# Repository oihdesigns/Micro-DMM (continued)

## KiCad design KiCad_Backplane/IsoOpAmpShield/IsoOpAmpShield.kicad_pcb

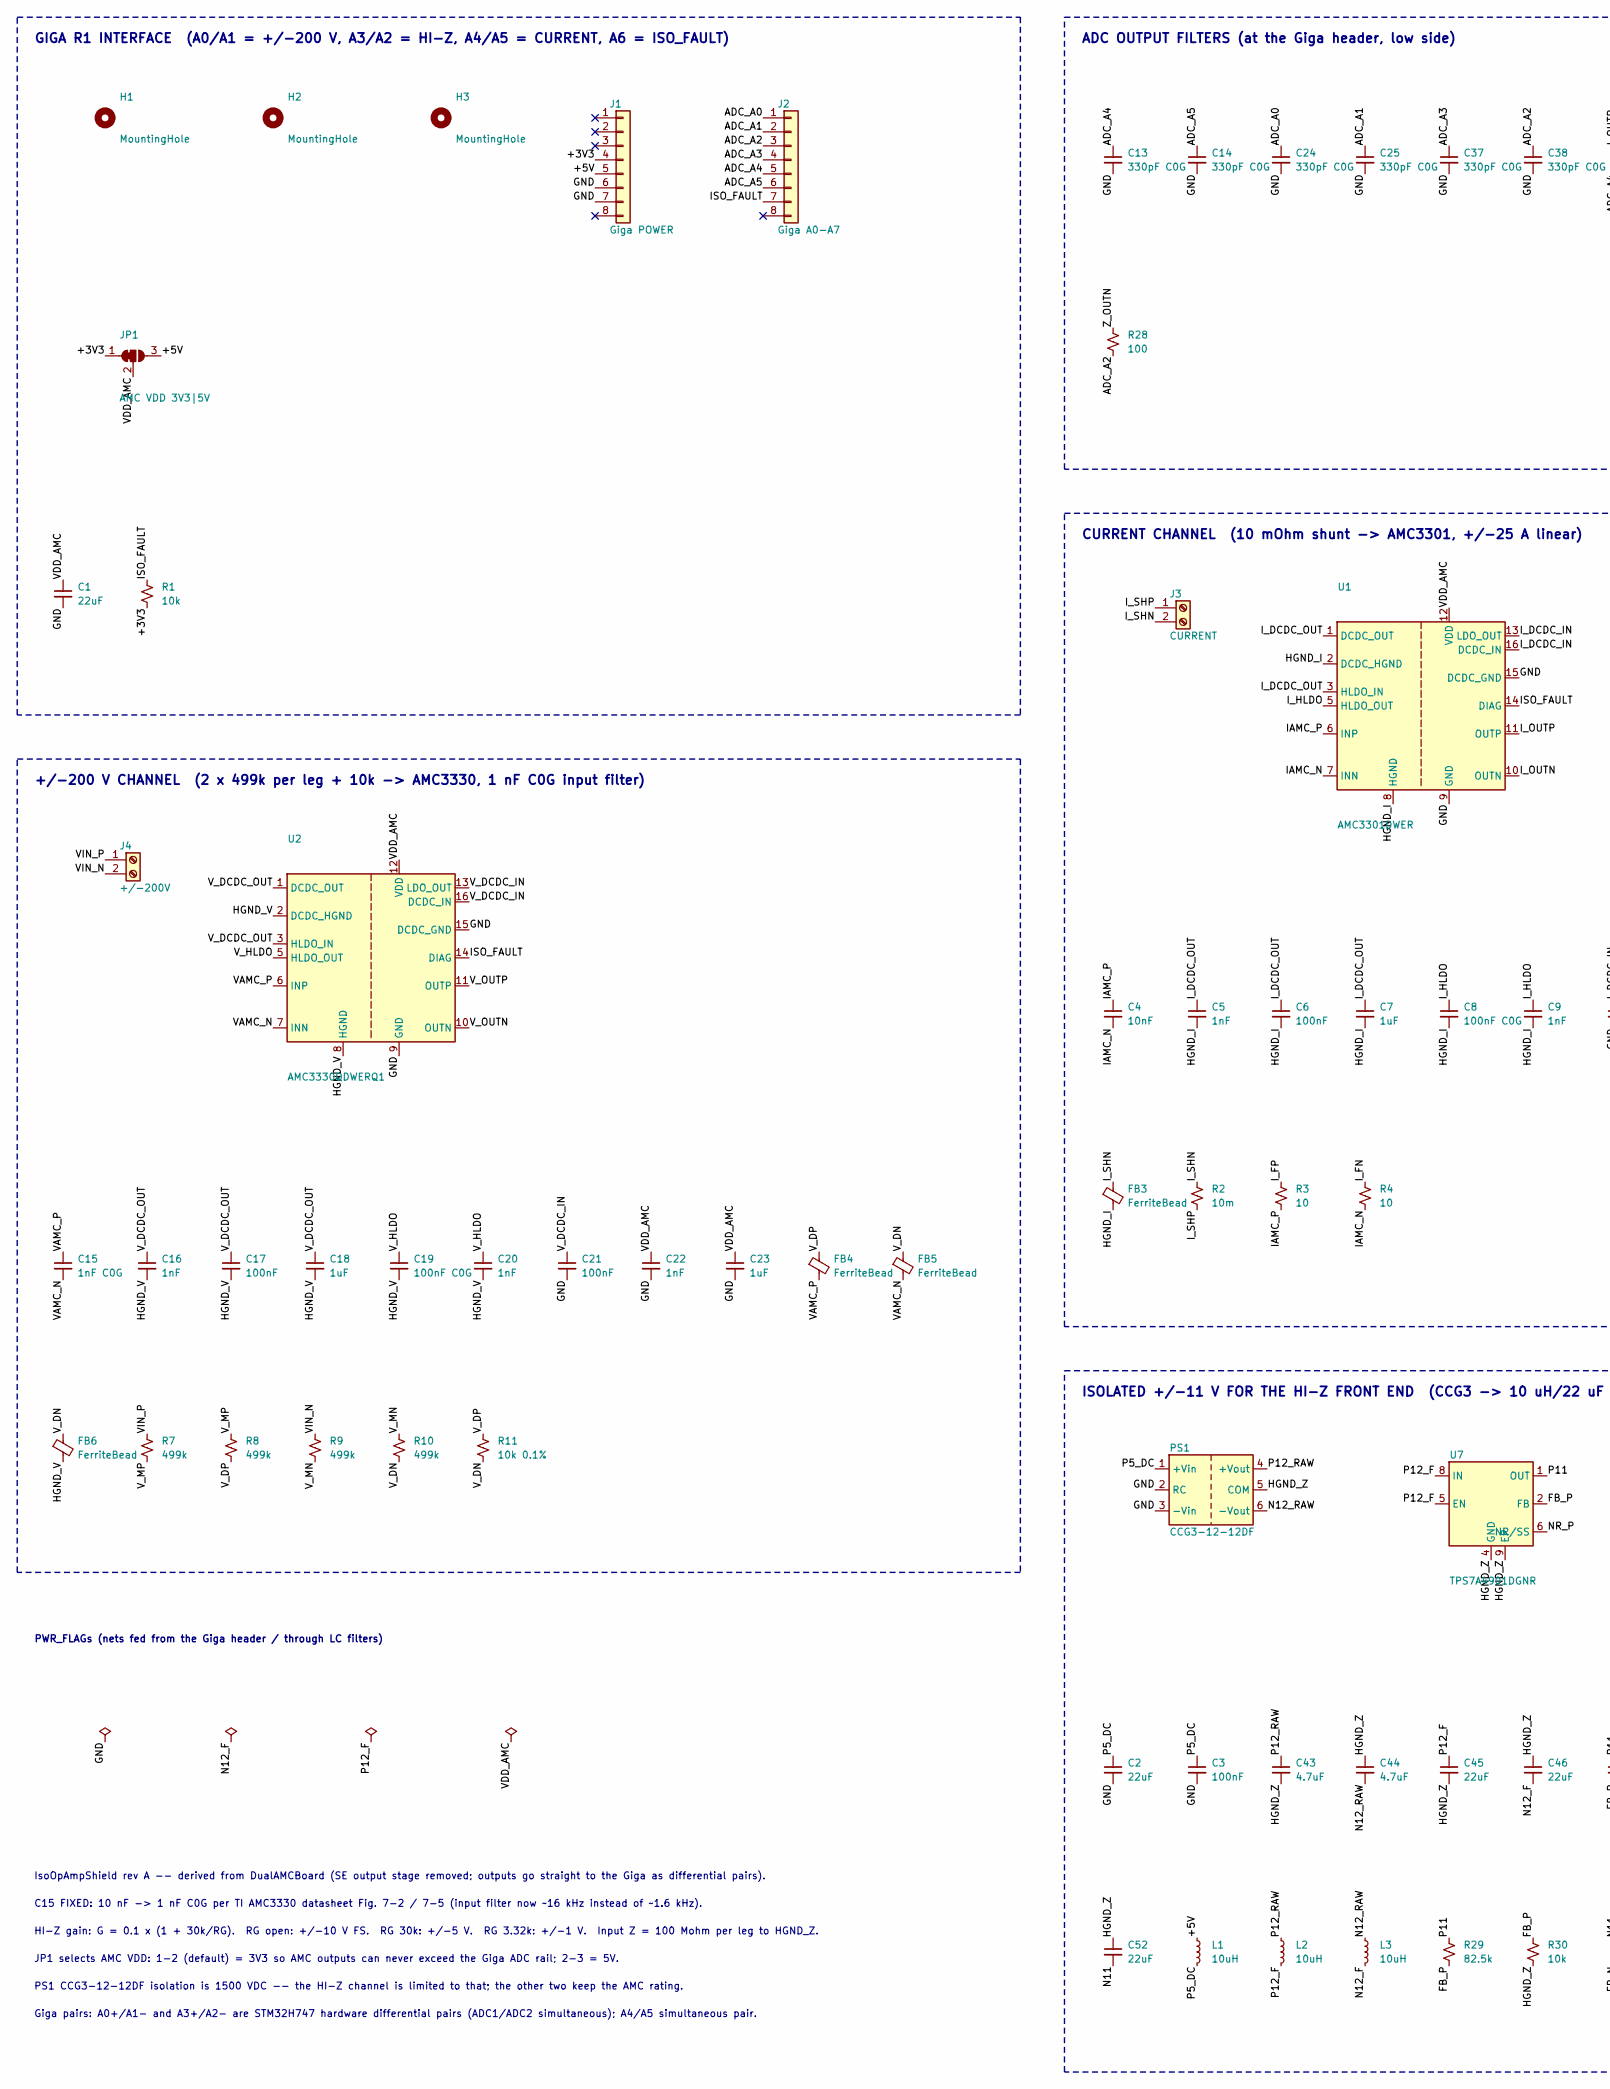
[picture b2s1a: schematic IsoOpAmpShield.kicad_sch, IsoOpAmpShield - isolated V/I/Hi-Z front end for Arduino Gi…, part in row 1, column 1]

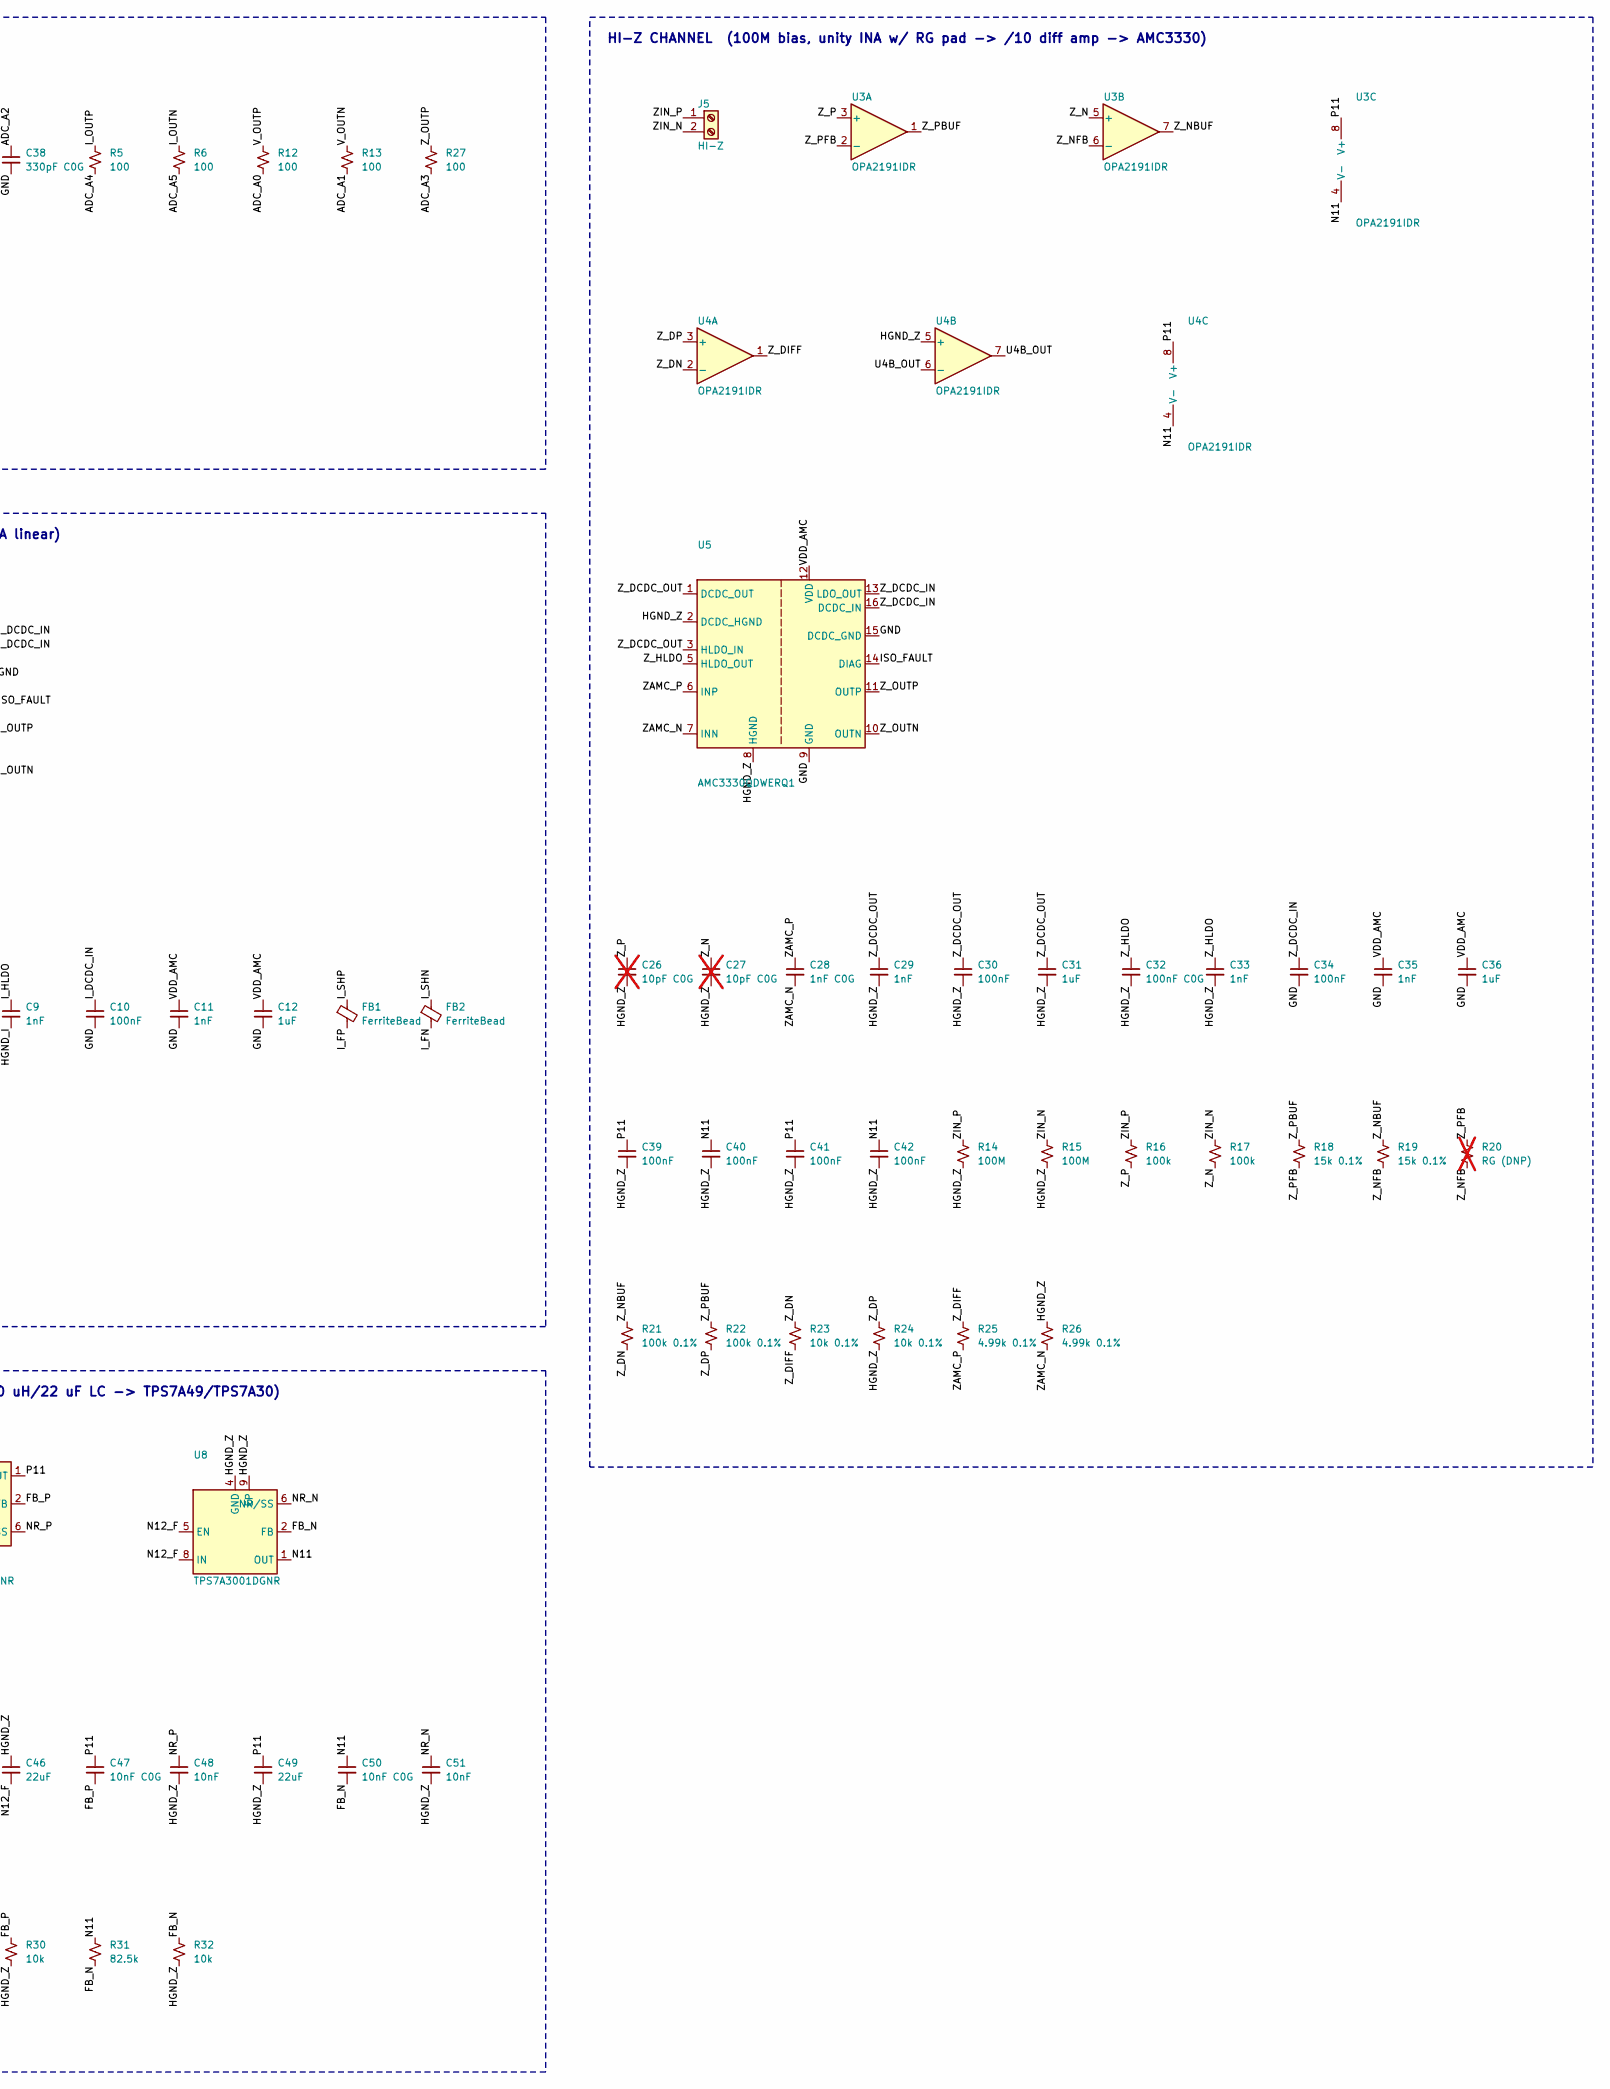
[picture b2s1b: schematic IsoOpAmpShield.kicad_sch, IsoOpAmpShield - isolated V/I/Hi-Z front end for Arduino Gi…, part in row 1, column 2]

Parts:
C1, C2, C45, C46, C49, C52: 22uF; C_0805_2012Metric_Pad1.18x1.45mm_HandSolder
C3, C6, C10, C17, C21, C30, C34, C39, C40, C41, C42: 100nF; C_0603_1608Metric_Pad1.08x0.95mm_HandSolder
C4: 10nF; C_0805_2012Metric_Pad1.18x1.45mm_HandSolder
C5, C16, C29: 1nF; C_0603_1608Metric_Pad1.08x0.95mm_HandSolder
C7, C18, C31: 1uF; C_0603_1608Metric_Pad1.08x0.95mm_HandSolder
C8, C19, C32: 100nF C0G; C_1206_3216Metric_Pad1.33x1.80mm_HandSolder
C9, C11, C20, C22, C33, C35: 1nF; C_1206_3216Metric_Pad1.33x1.80mm_HandSolder
C12, C23, C36: 1uF; C_1206_3216Metric_Pad1.33x1.80mm_HandSolder
C13, C14, C24, C25, C37, C38: 330pF C0G; C_0603_1608Metric_Pad1.08x0.95mm_HandSolder
C15, C28: 1nF C0G; C_0805_2012Metric_Pad1.18x1.45mm_HandSolder
C26, C27: 10pF C0G; C_0603_1608Metric_Pad1.08x0.95mm_HandSolder; not fitted
C43, C44: 4.7uF; C_0805_2012Metric_Pad1.18x1.45mm_HandSolder
C47, C50: 10nF C0G; C_0603_1608Metric_Pad1.08x0.95mm_HandSolder
C48, C51: 10nF; C_0603_1608Metric_Pad1.08x0.95mm_HandSolder
FB1, FB2, FB3, FB4, FB5, FB6: FerriteBead; L_0402_1005Metric_Pad0.77x0.64mm_HandSolder
H1, H2, H3: MountingHole; MountingHole_3.2mm_M3_Giga
J1: Giga POWER; PinHeader_1x08_P2.54mm_Vertical
J2: Giga A0-A7; PinHeader_1x08_P2.54mm_Vertical
J3: CURRENT; TerminalBlock_RND_205-00232_1x02_P5.08mm_Horizontal
J4: +/-200V; TerminalBlock_RND_205-00232_1x02_P5.08mm_Horizontal
J5: HI-Z; TerminalBlock_RND_205-00232_1x02_P5.08mm_Horizontal
JP1: AMC VDD 3V3|5V; SolderJumper-3_P1.3mm_Bridged12_RoundedPad1.0x1.5mm
L1, L2, L3: 10uH; L_1210_3225Metric_Pad1.42x2.65mm_HandSolder
PS1: CCG3-12-12DF; TDK_CCG3_Dual_THT
R1, R30, R32: 10k; R_0805_2012Metric_Pad1.20x1.40mm_HandSolder
R2: 10m; R_2010_5025Metric_Pad1.40x2.65mm_HandSolder
R3, R4: 10; R_0805_2012Metric_Pad1.20x1.40mm_HandSolder
R5, R6, R12, R13, R27, R28: 100; R_0805_2012Metric_Pad1.20x1.40mm_HandSolder
R7, R8, R9, R10: 499k; R_0805_2012Metric_Pad1.20x1.40mm_HandSolder
R11, R23, R24: 10k 0.1%; R_0805_2012Metric_Pad1.20x1.40mm_HandSolder
R14, R15: 100M; R_1206_3216Metric_Pad1.30x1.75mm_HandSolder
R16, R17: 100k; R_1206_3216Metric_Pad1.30x1.75mm_HandSolder
R18, R19: 15k 0.1%; R_0805_2012Metric_Pad1.20x1.40mm_HandSolder
R20: RG (DNP); R_0805_2012Metric_Pad1.20x1.40mm_HandSolder; not fitted
R21, R22: 100k 0.1%; R_0805_2012Metric_Pad1.20x1.40mm_HandSolder
R25, R26: 4.99k 0.1%; R_0805_2012Metric_Pad1.20x1.40mm_HandSolder
R29, R31: 82.5k; R_0805_2012Metric_Pad1.20x1.40mm_HandSolder
U1: AMC3301DWER; SOIC-16W_7.5x10.3mm_P1.27mm
U2, U5: AMC3330QDWERQ1; SOIC-16W_7.5x10.3mm_P1.27mm
U3, U4: OPA2191IDR; SOIC-8_3.9x4.9mm_P1.27mm
U7: TPS7A4901DGNR; HVSSOP-8-1EP_3x3mm_P0.65mm_EP1.57x1.89mm
U8: TPS7A3001DGNR; HVSSOP-8-1EP_3x3mm_P0.65mm_EP1.57x1.89mm

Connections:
/+3V3: J1.4, JP1.1 (A), R1.2
/+5V: J1.5, JP1.3 (B), L1.1
/ADC_A0: C24.1, J2.1, R12.2
/ADC_A1: C25.1, J2.2, R13.2
/ADC_A2: C38.1, J2.3, R28.2
/ADC_A3: C37.1, J2.4, R27.2
/ADC_A4: C13.1, J2.5, R5.2
/ADC_A5: C14.1, J2.6, R6.2
/FB_N: C50.2, R31.2, R32.1, U8.2 (FB)
/FB_P: C47.2, R29.2, R30.1, U7.2 (FB)
/GND: C1.2, C2.2, C3.2, C10.2, C11.2, C12.2, C13.2, C14.2, C21.2, C22.2, C23.2, C24.2, C25.2, C34.2, C35.2, C36.2, C37.2, C38.2, J1.6, J1.7, PS1.2 (RC), PS1.3 (-Vin), U1.9 (GND), U1.15 (DCDC_GND), U2.9 (GND), U2.15 (DCDC_GND), U5.9 (GND), U5.15 (DCDC_GND)
/HGND_I: C5.2, C6.2, C7.2, C8.2, C9.2, FB3.2, U1.2 (DCDC_HGND), U1.8 (HGND)
/HGND_V: C16.2, C17.2, C18.2, C19.2, C20.2, FB6.2, U2.2 (DCDC_HGND), U2.8 (HGND)
/HGND_Z: C26.2, C27.2, C29.2, C30.2, C31.2, C32.2, C33.2, C39.2, C40.2, C41.2, C42.2, C43.2, C44.1, C45.2, C46.1, C48.2, C49.2, C51.2, C52.1, PS1.5 (COM), R14.2, R15.2, R24.2, R26.1, R30.2, R32.2, U4.5 (+), U5.2 (DCDC_HGND), U5.8 (HGND), U7.4 (GND), U7.9 (EP), U8.4 (GND), U8.9 (EP)
/IAMC_N: C4.2, R4.2, U1.7 (INN)
/IAMC_P: C4.1, R3.2, U1.6 (INP)
/ISO_FAULT: J2.7, R1.1, U1.14 (DIAG), U2.14 (DIAG), U5.14 (DIAG)
/I_DCDC_IN: C10.1, U1.13 (LDO_OUT), U1.16 (DCDC_IN)
/I_DCDC_OUT: C5.1, C6.1, C7.1, U1.1 (DCDC_OUT), U1.3 (HLDO_IN)
/I_FN: FB2.2, R4.1
/I_FP: FB1.2, R3.1
/I_HLDO: C8.1, C9.1, U1.5 (HLDO_OUT)
/I_OUTN: R6.1, U1.10 (OUTN)
/I_OUTP: R5.1, U1.11 (OUTP)
/I_SHN: FB2.1, FB3.1, J3.2, R2.1
/I_SHP: FB1.1, J3.1, R2.2
/N11: C40.1, C42.1, C50.1, C52.2, R31.1, U3.4 (V-), U4.4 (V-), U8.1 (OUT)
/N12_F: C46.2, L3.2, U8.5 (EN), U8.8 (IN)
/N12_RAW: C44.2, L3.1, PS1.6 (-Vout)
/NR_N: C51.1, U8.6 (NR/SS)
/NR_P: C48.1, U7.6 (NR/SS)
/P5_DC: C2.1, C3.1, L1.2, PS1.1 (+Vin)
/P11: C39.1, C41.1, C47.1, C49.1, R29.1, U3.8 (V+), U4.8 (V+), U7.1 (OUT)
/P12_F: C45.1, L2.2, U7.5 (EN), U7.8 (IN)
/P12_RAW: C43.1, L2.1, PS1.4 (+Vout)
/U4B_OUT: U4.6 (-), U4.7
/VAMC_N: C15.2, FB5.2, U2.7 (INN)
/VAMC_P: C15.1, FB4.2, U2.6 (INP)
/VDD_AMC: C1.1, C11.1, C12.1, C22.1, C23.1, C35.1, C36.1, JP1.2 (C), U1.12 (VDD), U2.12 (VDD), U5.12 (VDD)
/VIN_N: J4.2, R9.1
/VIN_P: J4.1, R7.1
/V_DCDC_IN: C21.1, U2.13 (LDO_OUT), U2.16 (DCDC_IN)
/V_DCDC_OUT: C16.1, C17.1, C18.1, U2.1 (DCDC_OUT), U2.3 (HLDO_IN)
/V_DN: FB5.1, FB6.1, R10.2, R11.2
/V_DP: FB4.1, R8.2, R11.1
/V_HLDO: C19.1, C20.1, U2.5 (HLDO_OUT)
/V_MN: R9.2, R10.1
/V_MP: R7.2, R8.1
/V_OUTN: R13.1, U2.10 (OUTN)
/V_OUTP: R12.1, U2.11 (OUTP)
/ZAMC_N: C28.2, R26.2, U5.7 (INN)
/ZAMC_P: C28.1, R25.2, U5.6 (INP)
/ZIN_N: J5.2, R15.1, R17.1
/ZIN_P: J5.1, R14.1, R16.1
/Z_DCDC_IN: C34.1, U5.13 (LDO_OUT), U5.16 (DCDC_IN)
/Z_DCDC_OUT: C29.1, C30.1, C31.1, U5.1 (DCDC_OUT), U5.3 (HLDO_IN)
/Z_DIFF: R23.2, R25.1, U4.1
/Z_DN: R21.2, R23.1, U4.2 (-)
/Z_DP: R22.2, R24.1, U4.3 (+)
/Z_HLDO: C32.1, C33.1, U5.5 (HLDO_OUT)
/Z_N: C27.1, R17.2, U3.5 (+)
/Z_NBUF: R19.1, R21.1, U3.7
/Z_NFB: R19.2, R20.2, U3.6 (-)
/Z_OUTN: R28.1, U5.10 (OUTN)
/Z_OUTP: R27.1, U5.11 (OUTP)
/Z_P: C26.1, R16.2, U3.3 (+)
/Z_PBUF: R18.1, R22.1, U3.1
/Z_PFB: R18.2, R20.1, U3.2 (-)

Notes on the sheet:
GIGA R1 INTERFACE (A0/A1 = +/-200 V, A3/A2 = HI-Z, A4/A5 = CURRENT, A6 = ISO_FAULT)
+/-200 V CHANNEL (2 x 499k per leg + 10k -> AMC3330, 1 nF C0G input filter)
ADC OUTPUT FILTERS (at the Giga header, low side)
CURRENT CHANNEL (10 mOhm shunt -> AMC3301, +/-25 A linear)
ISOLATED +/-11 V FOR THE HI-Z FRONT END (CCG3 -> 10 uH/22 uF LC -> TPS7A49/TPS7A30)
HI-Z CHANNEL (100M bias, unity INA w/ RG pad -> /10 diff amp -> AMC3330)
PWR_FLAGs (nets fed from the Giga header / through LC filters)
IsoOpAmpShield rev A -- derived from DualAMCBoard (SE output stage removed; outputs go straight to the Giga as differential pairs).
C15 FIXED: 10 nF -> 1 nF C0G per TI AMC3330 datasheet Fig. 7-2 / 7-5 (input filter now ~16 kHz instead of ~1.6 kHz).
HI-Z gain: G = 0.1 x (1 + 30k/RG). RG open: +/-10 V FS. RG 30k: +/-5 V. RG 3.32k: +/-1 V. Input Z = 100 Mohm per leg to HGND_Z.
JP1 selects AMC VDD: 1-2 (default) = 3V3 so AMC outputs can never exceed the Giga ADC rail; 2-3 = 5V.
PS1 CCG3-12-12DF isolation is 1500 VDC -- the HI-Z channel is limited to that; the other two keep the AMC rating.
Giga pairs: A0+/A1- and A3+/A2- are STM32H747 hardware differential pairs (ADC1/ADC2 simultaneous); A4/A5 simultaneous pair.

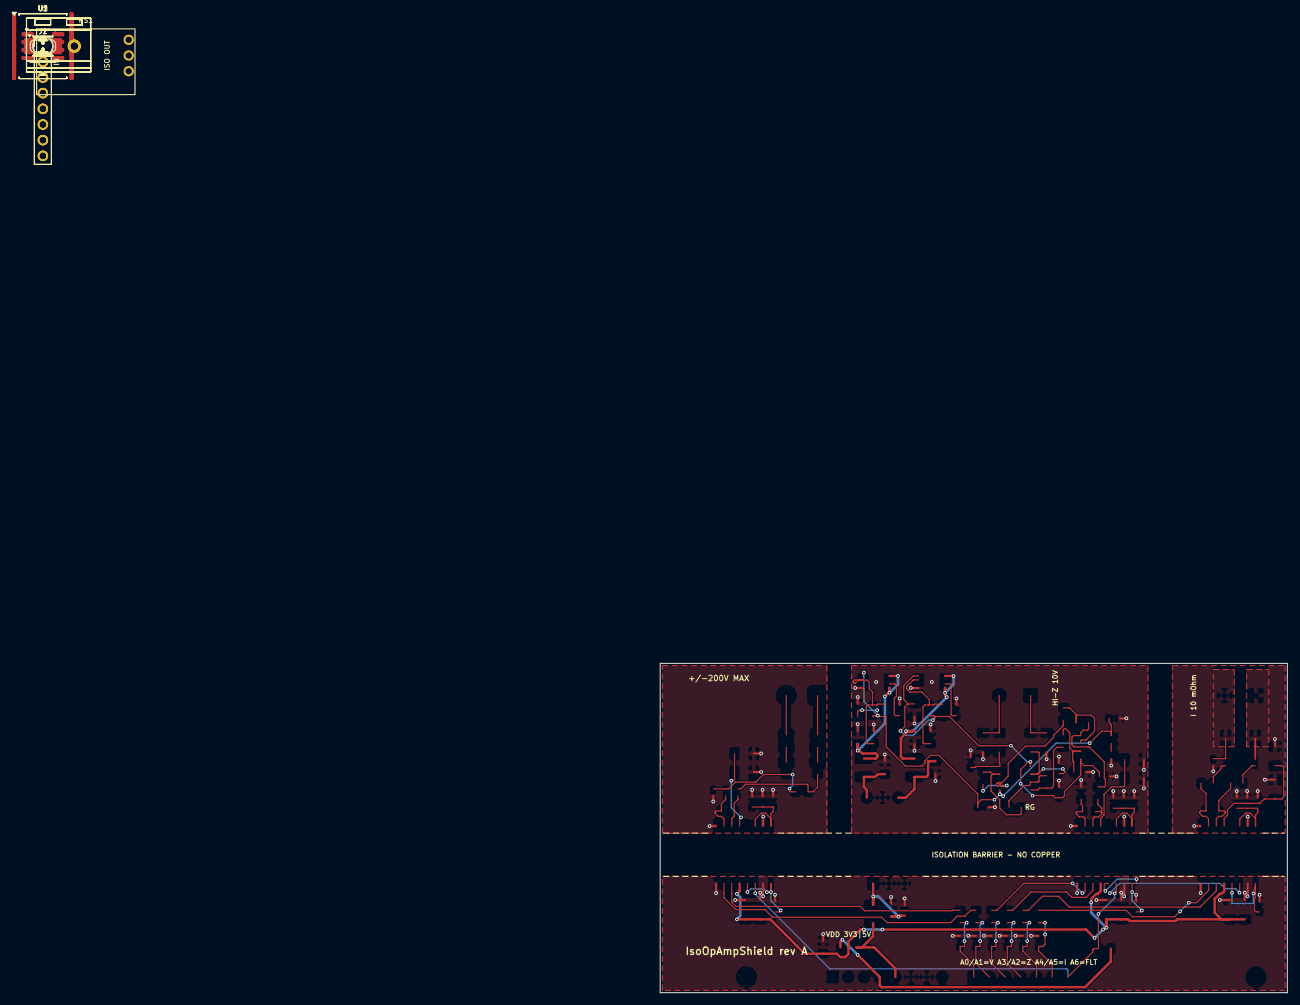
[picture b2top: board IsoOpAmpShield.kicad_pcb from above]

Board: 4 copper layers, 101.6 x 53.3 mm, 110 parts (0 on the bottom side), 68 nets.

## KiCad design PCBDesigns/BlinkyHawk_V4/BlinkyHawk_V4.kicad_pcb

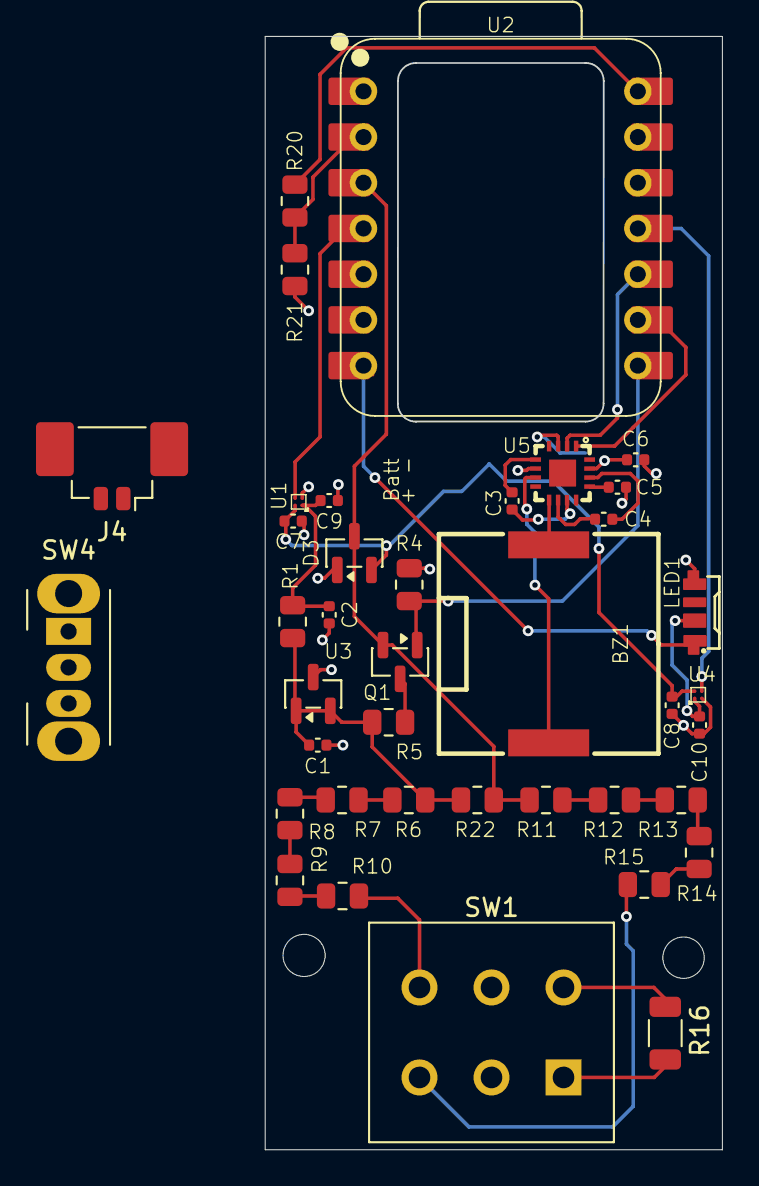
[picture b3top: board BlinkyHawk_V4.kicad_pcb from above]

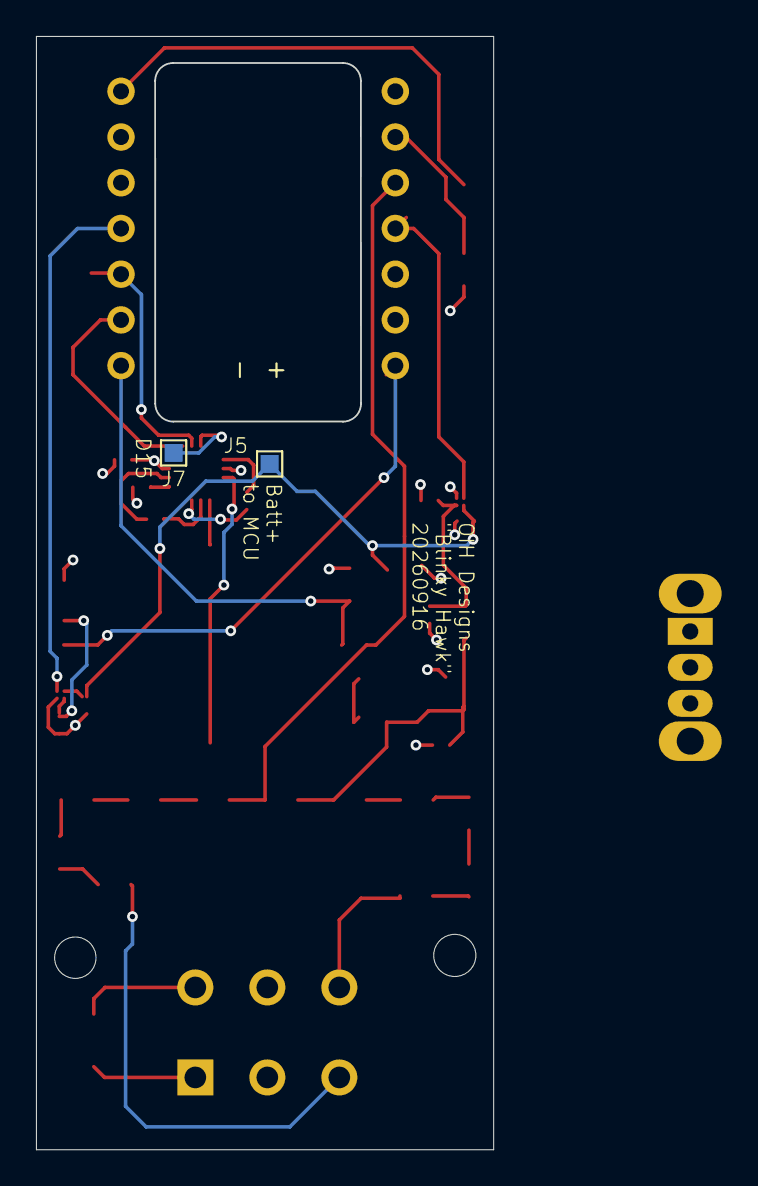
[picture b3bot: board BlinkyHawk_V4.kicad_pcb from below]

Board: 4 copper layers, 25.4 x 61.8 mm, 41 parts (2 on the bottom side), 37 nets.

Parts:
BZ1: Buzzer; BUZ-SMD_2P-L12.0-W12.0-L_PKLCS1212E4001-R1
C1, C9, C10: 0.1uF; C_0402_1005Metric
C2, C3, C4, C7, C8: 1uF; C_0402_1005Metric
C5, C6: 2.2uF; C_0402_1005Metric
D3: BAT54S; SOT-23
J4: Battery; Molex_PicoBlade_53398-0271_1x02-1MP_P1.25mm_Vertical
J5, J7: Conn_01x01; TestPoint_Pad_1.0x1.0mm
LED1: SK6812SIDE-A_C5378721; LED-SMD_4P-L4.0-W1.6-L
Q1: AO3400A MOSFET; SOT-23
R1: 4.7K; R_0805_2012Metric
R4, R5, R6, R7, R8, R9, R10, R11, R12, R13, R14, R15, R20, R21: 100K; R_0805_2012Metric
R16: 100K; R_1206_3216Metric
R22: 1Meg; R_0805_2012Metric
SW1: SW_Push_DPDT; SW_PUSH_E-Switch_FS5700DP_DPDT
SW4: SW_SPDT; SW_Slide_SPDT_Angled_CK_OS102011MA1Q
U1, U4: TPS22914BYFPR; DSBGA-4_L0.8-W0.8-R2-C2-P0.40-BL
U2: XIAO-R4-DIP
U3: TL431DBZ; SOT-23
U5: PAM8904JER; TQFN-16_L3.0-W3.0-P0.50-BL-EP1.5

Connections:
5vRail: C7.1, C8.1, D3.2 (K), R20.2, U1.A2 (VIN), U2.14 (5V), U4.A2 (VIN)
+3V3: C6.1, U2.12 (3V3), U5.15 (VIN)
A1: R20.1, R21.1, U2.2 (PA4_A1_D1)
A2: D3.3 (COM), Q1.2 (S), R11.2, R22.2, U2.3 (PA10_A2_D2)
A3: U1.B2 (ON), U2.4 (PA11_A3_D3)
Analog_Rail: C2.2, C9.2, R1.1, U1.A1 (VOUT)
Bridge_CRTL: Q1.1 (G), R4.2, U2.8 (PB09_A7_D7_RX)
D6: LED1.1 (DIN), U2.7 (PB08_A6_D6_TX)
D8: U2.9 (PA7_A8_D8_SCK), U5.1 (EN1)
D9: U2.10 (PA5_A9_D9_MISO), U5.2 (EN2)
D10: U2.11 (PA6_A10_D10_MOSI), U4.B2 (ON)
D15: J7.1 (Pin_1_1), U5.3 (DIN)
Gnd: C1.1, C2.1, C5.2, C6.2, C7.2, C8.2, C9.1, C10.1, D3.1 (A), J4.1, LED1.4 (GND), R4.1, R21.2, U1.B1 (GND), U2.13 (GND), U3.3 (A), U4.B1 (GND), U5.6 (GND)
LEDRail: C10.2, LED1.2 (VDD), U4.A1 (VOUT)
unnamed: BZ1.1 (+), U5.9 (VO1)
unnamed: BZ1.2 (-), U5.7 (VO2)
unnamed: J4.2, SW4.1 (A)
unnamed: J5.1 (Pin_1_1), SW4.2 (B)
unnamed: Q1.3 (D), R5.1
unnamed: R6.1, R7.2
unnamed: R7.1, R8.2
unnamed: R8.1, R9.2
unnamed: R9.1, R10.2
unnamed: R11.1, R12.2
unnamed: R12.1, R13.2
unnamed: R13.1, R14.2
unnamed: R14.1, R15.2
unnamed: R16.1, SW1.1 (A)
unnamed: R16.2, SW1.4 (A)
unnamed: C1.2, R1.2, R5.2, R6.2, R22.1, U3.1 (K), U3.2 (REF)
unnamed: C3.2, U5.5 (CN1)
unnamed: C4.2, U5.10 (CN2)
unnamed: C3.1, U5.11 (CP1)
unnamed: C4.1, U5.14 (CP2)
unnamed: C5.1, U5.13 (VOUT)
V_Input_Float: R15.1, SW1.3 (C)
V_Input_REF: R10.1, SW1.6 (C)
